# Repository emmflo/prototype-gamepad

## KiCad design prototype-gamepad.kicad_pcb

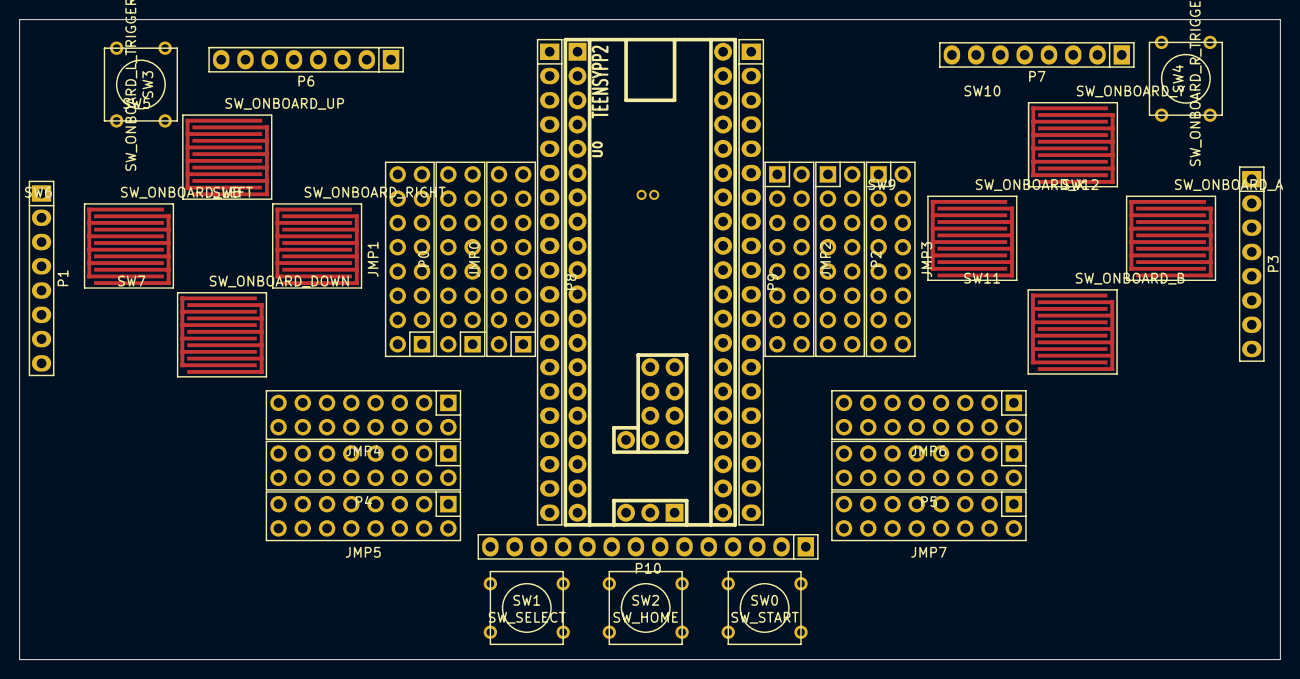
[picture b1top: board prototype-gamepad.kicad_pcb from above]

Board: 2 copper layers, 132.0 x 67.0 mm, 33 parts (0 on the bottom side), 115 nets, no tracks yet.

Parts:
JMP0, JMP1, JMP4, JMP5: JUMPERS_8X2; Pin_Header_Straight_2x08
JMP2, JMP3: TOP_RIGHT_8X2; Pin_Header_Straight_2x08
JMP6, JMP7: BOTTOM_RIGHT_8X2; Pin_Header_Straight_2x08
P0: TOP_LEFT_8X2; Pin_Header_Straight_2x08
P1: TOP_LEFT_8; Pin_Header_Straight_1x08
P2: TOP_RIGHT_8X2; Pin_Header_Straight_2x08
P3: TOP_RIGHT_8; Pin_Header_Straight_1x08
P4: BOTTOM_LEFT_8X2; Pin_Header_Straight_2x08
P5: BOTTOM_RIGHT_8X2; Pin_Header_Straight_2x08
P6: TRIGGER_LEFT_8; Pin_Header_Straight_1x08
P7: TRIGGER_RIGHT_8; Pin_Header_Straight_1x08
P8, P9: CONN_20; Pin_Header_Straight_1x20
P10: CONN_14; Pin_Header_Straight_1x14
SW0: SW_START; SW_PUSH_SMALL
SW1: SW_SELECT; SW_PUSH_SMALL
SW2: SW_HOME; SW_PUSH_SMALL
SW3: SW_ONBOARD_L_TRIGGER; SW_PUSH_SMALL
SW4: SW_ONBOARD_R_TRIGGER; SW_PUSH_SMALL
SW5: SW_ONBOARD_UP; SW_RUBBER_PCB_CONTACT
SW6: SW_ONBOARD_LEFT; SW_RUBBER_PCB_CONTACT
SW7: SW_ONBOARD_DOWN; SW_RUBBER_PCB_CONTACT
SW8: SW_ONBOARD_RIGHT; SW_RUBBER_PCB_CONTACT
SW9: SW_ONBOARD_X; SW_RUBBER_PCB_CONTACT
SW10: SW_ONBOARD_Y; SW_RUBBER_PCB_CONTACT
SW11: SW_ONBOARD_B; SW_RUBBER_PCB_CONTACT
SW12: SW_ONBOARD_A; SW_RUBBER_PCB_CONTACT
U0: TEENSYPP2

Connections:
/ALE: JMP7.6, P10.5, U0.30
/AREF: P9.12, U0.41
/GND: JMP0.15, JMP2.15, JMP4.15, JMP6.15, P1.1, P1.2, P1.3, P1.4, P1.5, P1.6, P1.7, P1.8, P3.1, P3.2, P3.3, P3.4, P3.5, P3.6, P3.7, P3.8, P6.8, P7.8, P8.1, SW0.2, SW1.2, SW2.2, SW3.2, SW4.2, SW5.2, SW6.2, SW7.2, SW8.2, SW9.2, SW10.2, SW11.2, SW12.2, U0.1, U0.22, U0.42
/PA0: JMP1.2, P10.10, SW5.1, U0.25
/PA1: JMP1.4, P10.8, SW6.1, U0.27
/PA2: JMP1.6, P10.6, SW7.1, U0.29
/PA3: JMP1.8, P10.3, SW8.1, U0.32
/PA4: JMP1.10, P10.11, U0.24
/PA5: JMP1.12, P10.9, U0.26
/PA6: JMP1.14, P10.7, U0.28
/PA7: JMP1.16, P10.4, U0.31
/PB0: JMP3.2, P9.8, U0.45
/PB1: JMP3.4, P9.7, SW10.1, U0.46
/PB2: JMP3.6, P9.6, SW11.1, U0.47
/PB3: JMP3.8, P9.5, SW12.1, U0.48
/PB4: JMP3.10, P9.4, U0.49
/PB5: JMP3.12, P9.3, U0.50
/PB6: JMP3.14, P9.2, U0.51
/PB7: JMP3.16, P8.2, SW2.1, U0.2
/PC0: JMP5.2, P8.13, U0.13
/PC1: JMP5.4, P8.14, U0.14
/PC2: JMP5.6, P8.15, U0.15
/PC3: JMP5.8, P8.16, U0.16
/PC4: JMP5.10, P8.17, U0.17
/PC5: JMP5.12, P8.18, U0.18
/PC6: JMP5.14, P8.19, U0.19
/PC7: JMP5.16, P8.20, U0.20
/PD0: JMP0.11, JMP2.11, JMP4.11, JMP6.11, P6.4, P7.4, P8.3, SW9.1, U0.3
/PD1: JMP0.13, JMP2.13, JMP4.13, JMP6.13, P6.5, P7.5, P8.4, U0.4
/PD2: P6.6, P8.5, SW3.1, U0.5
/PD3: P6.7, P8.6, U0.6
/PD4: P7.6, P8.7, SW4.1, U0.7
/PD5: P7.7, P8.8, U0.8
/PD6: JMP7.16, P8.9, SW0.1, U0.9
/PD7: P8.10, SW1.1, U0.10
/PE0: JMP7.2, P8.11, U0.11
/PE1: JMP7.4, P8.12, U0.12
/PE4: JMP7.8, P10.1, U0.53
/PE5: JMP7.10, P10.2, U0.54
/PE6: JMP7.12, P9.10, U0.43
/PE7: JMP7.14, P9.9, U0.44
/PF0: JMP0.3, JMP4.7, P9.13, U0.40
/PF1: JMP0.5, JMP4.9, P9.14, U0.39
/PF2: JMP0.7, JMP4.3, P6.2, P9.15, U0.38
/PF3: JMP0.9, JMP4.5, P6.3, P9.16, U0.37
/PF4: JMP2.3, JMP6.7, P9.17, U0.36
/PF5: JMP2.5, JMP6.9, P9.18, U0.35
/PF6: JMP2.7, JMP6.3, P7.2, P9.19, U0.34
/PF7: JMP2.9, JMP6.5, P7.3, P9.20, U0.33
/RST: P10.12, U0.23
/VCC: JMP0.1, JMP2.1, JMP4.1, JMP6.1, P6.1, P7.1, P9.1, U0.21, U0.52
unnamed: JMP0.2, P0.1
unnamed: JMP0.4, P0.3
unnamed: JMP0.6, P0.5
unnamed: JMP0.8, P0.7
unnamed: JMP0.10, P0.9
unnamed: JMP0.12, P0.11
unnamed: JMP0.14, P0.13
unnamed: JMP0.16, P0.15
unnamed: JMP1.1, P0.2
unnamed: JMP1.3, P0.4
unnamed: JMP1.5, P0.6
unnamed: JMP1.7, P0.8
unnamed: JMP1.9, P0.10
unnamed: JMP1.11, P0.12
unnamed: JMP1.13, P0.14
unnamed: JMP1.15, P0.16
unnamed: JMP2.2, P2.1
unnamed: JMP2.4, P2.3
unnamed: JMP2.6, P2.5
unnamed: JMP2.8, P2.7
unnamed: JMP2.10, P2.9
unnamed: JMP2.12, P2.11
unnamed: JMP2.14, P2.13
unnamed: JMP2.16, P2.15
unnamed: JMP3.1, P2.2
unnamed: JMP3.3, P2.4
unnamed: JMP3.5, P2.6
unnamed: JMP3.7, P2.8
unnamed: JMP3.9, P2.10
unnamed: JMP3.11, P2.12
unnamed: JMP3.13, P2.14
unnamed: JMP3.15, P2.16
unnamed: JMP4.2, P4.1
unnamed: JMP4.4, P4.3
unnamed: JMP4.6, P4.5
unnamed: JMP4.8, P4.7
unnamed: JMP4.10, P4.9
unnamed: JMP4.12, P4.11
unnamed: JMP4.14, P4.13
unnamed: JMP4.16, P4.15
unnamed: JMP5.1, P4.2
unnamed: JMP5.3, P4.4
unnamed: JMP5.5, P4.6
unnamed: JMP5.7, P4.8
unnamed: JMP5.9, P4.10
unnamed: JMP5.11, P4.12
unnamed: JMP5.13, P4.14
unnamed: JMP5.15, P4.16
unnamed: JMP6.2, P5.1
unnamed: JMP6.4, P5.3
unnamed: JMP6.6, P5.5
unnamed: JMP6.8, P5.7
unnamed: JMP6.10, P5.9
unnamed: JMP6.12, P5.11
unnamed: JMP6.14, P5.13
unnamed: JMP6.16, P5.15
unnamed: JMP7.1, P5.2
unnamed: JMP7.3, P5.4
unnamed: JMP7.5, P5.6
unnamed: JMP7.7, P5.8
unnamed: JMP7.9, P5.10
unnamed: JMP7.11, P5.12
unnamed: JMP7.13, P5.14
unnamed: JMP7.15, P5.16

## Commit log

2015-01-29 initial project version
